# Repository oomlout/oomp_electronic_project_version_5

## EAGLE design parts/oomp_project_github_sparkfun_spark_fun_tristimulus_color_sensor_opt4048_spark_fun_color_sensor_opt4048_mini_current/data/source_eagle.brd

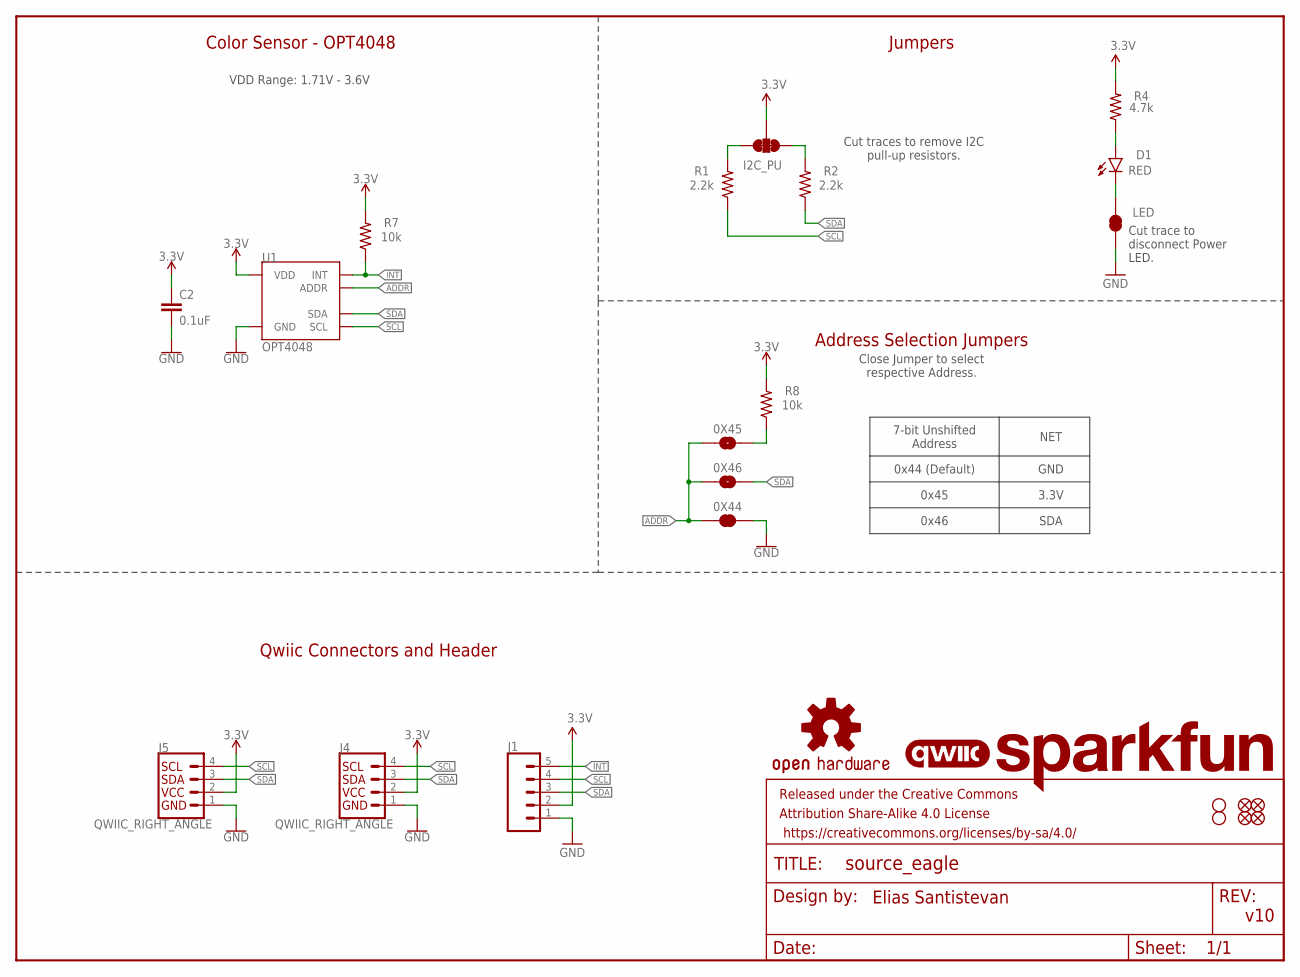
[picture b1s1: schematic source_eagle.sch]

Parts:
0X44: JUMPER-SMT_2_NC_TRACE_SILK; SMT-JUMPER_2_NC_TRACE_SILK
0X45, 0X46: JUMPER-SMT_2_NO_SILK; SMT-JUMPER_2_NO_SILK
C2: 0.1uF; 0402-TIGHT
D1: RED; LED-0603
FD5, FD6, FD7, FD8: FIDUCIALUFIDUCIAL; FIDUCIAL-MICRO
FRAME2: FRAME-LETTER; CREATIVE_COMMONS
H7, H8: STAND-OFFTIGHT; STAND-OFF-TIGHT
I2C_PU: S_MODE; SMT-JUMPER_3_2-NC_TRACE_SILK
J1: CONN_05NO_SILK; 1X05_NO_SILK
J4, J5: QWIIC_RIGHT_ANGLE; JST04_1MM_RA
LED: JUMPER-SMT_2_NC_TRACE_SILK; SMT-JUMPER_2_NC_TRACE_SILK
LOGO1: SFE_LOGO_NAMEBLANK; BLANK
LOGO2: QWIIC_LOGO_3MM; QWIIC_3MM
LOGO3: OSHW-LOGONO_SILK; DUMMY
R1, R2: 2.2k; 0603
R4: 4.7k; 0603
R7, R8: 10k; 0603
U1: OPT4048; FCSOT

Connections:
3.3V: C2.1, I2C_PU.2, J1.2, J4.2, J5.2, R4.2, R7.2, R8.2, U1.P1 (VDD)
ADDR: 0X44.1, 0X45.1, 0X46.1, U1.P2 (ADDR)
GND: 0X44.2, C2.2, J1.1, J4.1, J5.1, LED.1, U1.P4 (GND)
INT: J1.5, R7.1, U1.P7 (INT)
unnamed: I2C_PU.1, R1.2
unnamed: I2C_PU.3, R2.2
unnamed: D1.A, R4.1
unnamed: D1.C, LED.2
unnamed: 0X45.2, R8.1
SCL: J1.4, J4.4, J5.4, R1.1, U1.P5 (SCL)
SDA: 0X46.2, J1.3, J4.3, J5.3, R2.1, U1.P8 (SDA)

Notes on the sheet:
v10
Qwiic Connectors and Header
Elias Santistevan
Color Sensor - OPT4048
Cut traces to remove I2C pull-up resistors.
VDD Range: 1.71V - 3.6V
Jumpers
Cut trace to disconnect Power LED.
7-bit Unshifted Address
0x44 (Default)
0x45
0x46
GND
3.3V
SDA
NET
Address Selection Jumpers
Close Jumper to select respective Address.

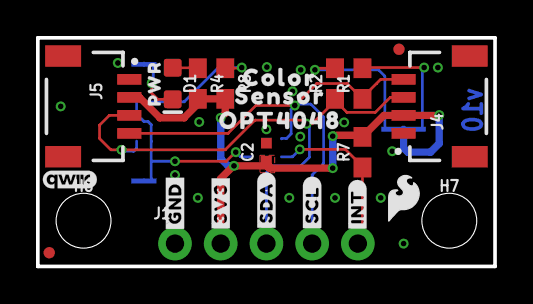
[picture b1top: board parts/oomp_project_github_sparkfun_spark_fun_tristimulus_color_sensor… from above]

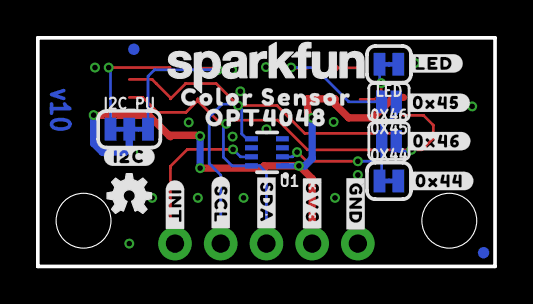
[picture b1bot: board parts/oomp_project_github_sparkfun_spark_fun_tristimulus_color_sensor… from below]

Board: 2 copper layers, 25.4 x 12.7 mm, 51 parts (22 on the bottom side), 11 nets.

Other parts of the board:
LOGO4: SPECIAL_INSTRUCTIONS-ORDERING; ORDERING_INSTRUCTIONS
U$1: #INT#9
U$2: COLOR_SENSOR227
U$3, U$12: OPT4048229
U$4: #0X44#11
U$5: #0X46#11
U$6: #0X45#11
U$7: #INT#3
U$8: SFE_LOGO_NAME_.1
U$9: COLOR14
U$10, U$37: #3V3#0
U$11: SENSOR15
U$13: #SDA#1
U$14: #LED#11
U$15: OSHW-LOGO-MINI
U$16, U$38: #GND#4
U$19, U$39: #SCL#5
U$20: #I2C#11
U$35: SFE_LOGO_FLAME_.1
U$40: #SDA#6
U$43: PWR8821882023

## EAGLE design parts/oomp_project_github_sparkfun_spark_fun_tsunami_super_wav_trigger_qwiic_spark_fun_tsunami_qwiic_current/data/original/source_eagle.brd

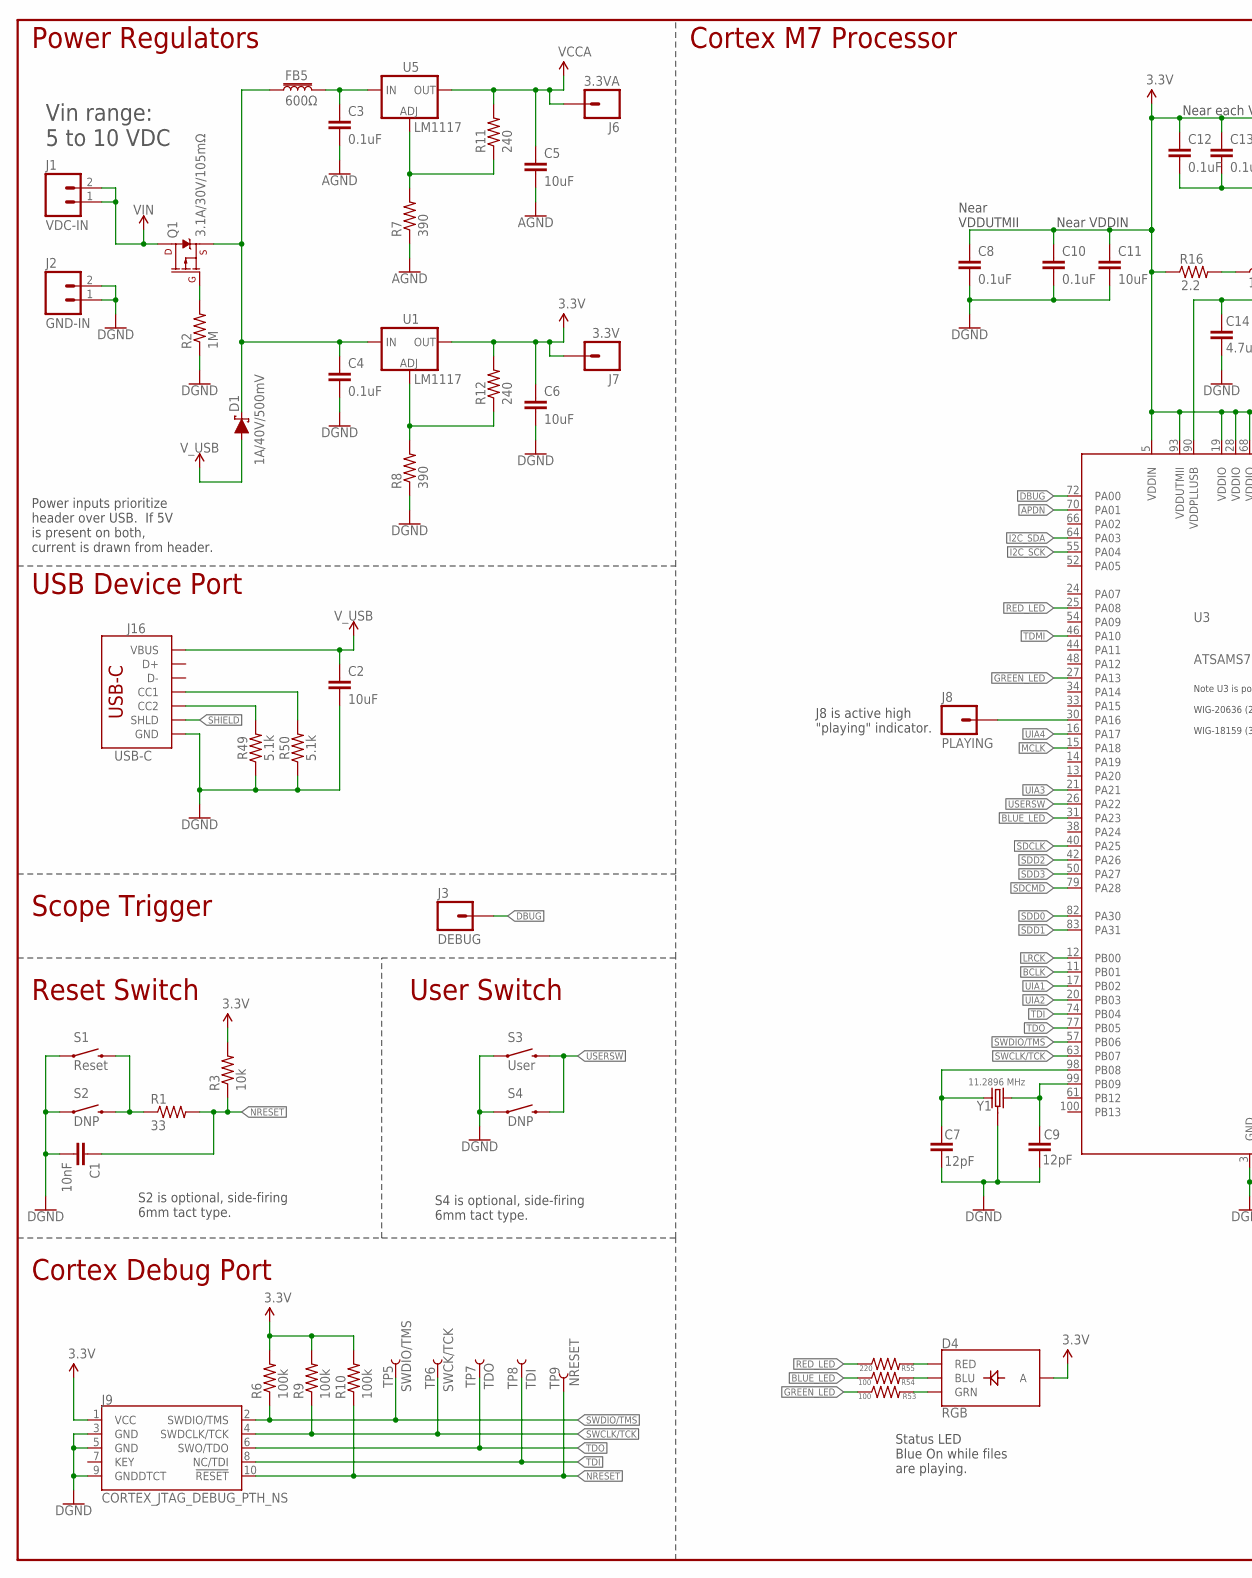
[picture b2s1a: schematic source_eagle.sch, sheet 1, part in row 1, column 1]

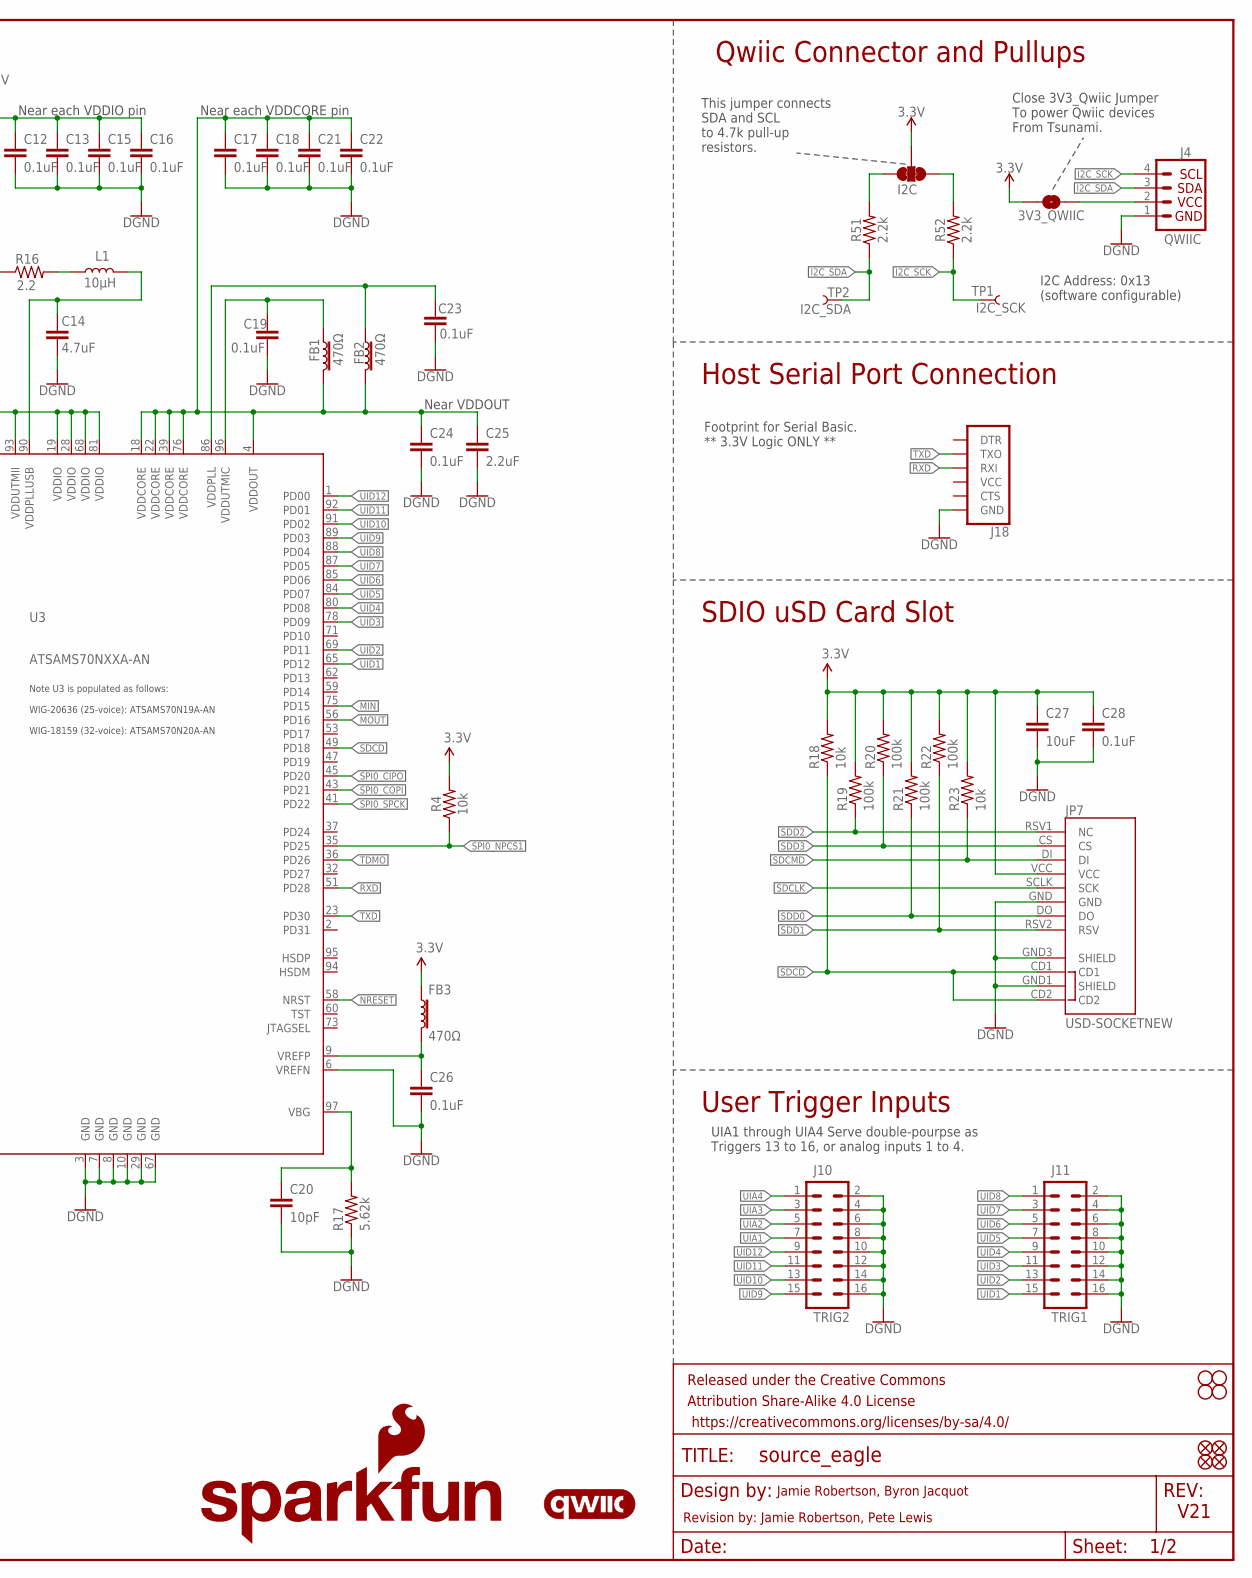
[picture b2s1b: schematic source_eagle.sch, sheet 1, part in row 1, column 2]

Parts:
3V3_QWIIC: JUMPER-SMT_2_NO_SILK; SMT-JUMPER_2_NO_SILK
C1: 10nF; 0402-TIGHT
C2, C5, C6, C11, C27: 10uF; 0402-TIGHT
C3, C4, C8, C10, C12, C13, C15, C16, C17, C18, C19, C21, C22, C23, C24, C26, C28: 0.1uF; 0402-TIGHT
C7, C9: 12pF; 0402-TIGHT
C14: 4.7uF; 0402-TIGHT
C20: 10pF; 0603
C25: 2.2uF; 0603
D1: 1A/40V/500mV; SMA-DIODE
D4: RGB; P-LCC-4-3
FB1, FB2, FB3: 470Ω; 0603
FB5: 600Ω; 0805
FD1, FD2, FD3, FD4: FIDUCIALUFIDUCIAL; FIDUCIAL-MICRO
FRAME1: FRAME-LEDGER; CREATIVE_COMMONS
H1, H2, H3, H4: STAND-OFF
I2C: JUMPER-SMT_3_2-NC_TRACE_SILK; SMT-JUMPER_3_2-NC_TRACE_SILK
J1: VDC-IN; 1X02_NO_SILK
J2: GND-IN; 1X02_NO_SILK
J3: DEBUG; 1X01_NO_SILK
J4: QWIIC; JST04_1MM_RA
J6: 3.3VA; 1X01_NO_SILK
J7: 3.3V; 1X01_NO_SILK
J8: PLAYING; 1X01_NO_SILK
J9: CORTEX_JTAG_DEBUG_PTH_NS; 2X5-PTH-1.27MM-NO_SILK
J10: TRIG2; 2X8_NOSILK
J11: TRIG1; 2X8_NOSILK
J16: USB-C; USB-C-16P-4LAYER-ISOLATED
J18: 6_PIN_SERIAL_TARGETSILK; 6_PIN_SERIAL_TARGET_SIDE_W_SILK
JP7: USD-SOCKETNEW; MICRO-SD-SOCKET-PP
L1: 10μH; 0805
LOGO2: SFE_LOGO_NAME_FLAME.2_INCH; SFE_LOGO_NAME_FLAME_.2
LOGO3: QWIIC_LOGO_4MM; QWIIC_4MM
Q1: 3.1A/30V/105mΩ; SOT23-3
R1: 33; 0603
R2: 1M; 0603
R3, R4, R18, R23: 10k; 0402-TIGHT
R6, R9, R10, R19, R20, R21, R22: 100k; 0402-TIGHT
R7, R8: 390; 0603
R11, R12: 240; 0603
R16: 2.2; 0603
R17: 5.62k; 0603
R49, R50: 5.1k; 0402-TIGHT
R51, R52: 2.2k; 0402-TIGHT
R53, R54: 100; 0603
R55: 220; 0603
S1: Reset; TACTILE_SWITCH_SMD_5.2MM
S2, S4: DNP; TACTILE_SWITCH_PTH_RIGHT_ANGLE
S3: User; TACTILE_SWITCH_SMD_5.2MM
TP1: I2C_SCK; TP_15TH
TP2: I2C_SDA; TP_15TH
TP5: SWDIO/TMS; TP_15TH
TP6: SWCK/TCK; TP_15TH
TP7: TDO; TP_15TH
TP8: TDI; TP_15TH
TP9: NRESET; TP_15TH
U1, U5: LM1117; SOT223
U3: ATSAMS70NXXA-AN; LQFP100
Y1: 11.2896 MHz; CRYSTAL-OSC-SMD-5X3

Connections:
3.3V: 3V3_QWIIC.1, C6.1, C8.1, C10.1, C11.1, C12.1, C13.1, C15.1, C16.1, C27.1, C28.1, D4.4 (A), FB3.1, I2C.2, J7.1, J9.1 (VCC), JP7.VCC, R3.2, R4.2, R6.2, R9.2, R10.2, R12.2, R16.1, R18.2, R19.2, R20.2, R21.2, R22.2, R23.2, U1.2 (OUT), U1.4 (OUT), U3.5 (VDDIN), U3.19 (VDDIO), U3.28 (VDDIO), U3.68 (VDDIO), U3.81 (VDDIO), U3.93 (VDDUTMII); also elsewhere on the board
AGND: C3.2, C5.2, R7.1; also elsewhere on the board
APDN: U3.70 (PA01); also elsewhere on the board
BCLK: U3.11 (PB01); also elsewhere on the board
BLUE_LED: R54.1, U3.31 (PA23)
CC1: J16.A5 (CC1), R50.2
CC2: J16.B5 (CC2), R49.2
DBUG: J3.1, U3.72 (PA00)
DGND: C1.2, C2.2, C4.2, C6.2, C7.2, C8.2, C9.2, C10.2, C11.2, C12.2, C13.2, C14.2, C15.2, C16.2, C17.2, C18.2, C19.2, C20.2, C21.2, C22.2, C23.2, C24.2, C25.2, C26.2, C27.2, C28.2, J2.1, J2.2, J4.1, J9.3 (GND), J9.5 (GND), J9.9 (GNDDTCT), J10.2, J10.4, J10.6, J10.8, J10.10, J10.12, J10.14, J10.16, J11.2, J11.4, J11.6, J11.8, J11.10, J11.12, J11.14, J11.16, J16.GND, J16.GND2 (GND), J18.6 (GND), JP7.GND, JP7.GND1 (SHIELD), JP7.GND3 (SHIELD), R2.1, R8.1, R17.1, R49.1, R50.1, S1.1, S2.1, S3.1, S4.1, U3.3 (GND), U3.6 (VREFN), U3.7 (GND), U3.8 (GND), U3.10 (GND), U3.29 (GND), U3.67 (GND), Y1.2 (3), Y1.4 (3); also elsewhere on the board
GREEN_LED: R53.1, U3.27 (PA13)
I2C_SCK: J4.4, R52.1, TP1.1, U3.55 (PA04)
I2C_SDA: J4.3, R51.1, TP2.1, U3.64 (PA03)
LRCK: U3.12 (PB00); also elsewhere on the board
MCLK: U3.15 (PA18); also elsewhere on the board
MIN: U3.75 (PD15); also elsewhere on the board
MOUT: U3.56 (PD16); also elsewhere on the board
unnamed: C7.1, U3.98 (PB08), Y1.1
unnamed: C9.1, U3.99 (PB09), Y1.3 (2)
unnamed: C19.1, FB1.1, U3.96 (VDDUTMIC)
unnamed: C14.1, L1.2, U3.90 (VDDPLLUSB)
unnamed: C23.1, FB2.1, U3.86 (VDDPLL)
unnamed: I2C.3, R51.2
unnamed: J8.1, U3.30 (PA16)
unnamed: I2C.1, R52.2
unnamed: C20.1, R17.2, U3.97 (VBG)
unnamed: C26.1, FB3.2, U3.9 (VREFP)
unnamed: L1.1, R16.2
unnamed: R7.2, R11.1, U5.1 (ADJ)
unnamed: R1.1, S1.3 (2), S2.2
unnamed: R8.2, R12.1, U1.1 (ADJ)
unnamed: 3V3_QWIIC.2, J4.2
unnamed: D4.2 (GRN), R53.2
unnamed: D4.3 (BLU), R54.2
unnamed: D4.1 (RED), R55.2
unnamed: C3.1, FB5.2, U5.3 (IN)
unnamed: Q1.1 (G), R2.2
NRESET: C1.1, J9.10 (!RESET), R1.2, R3.1, R10.1, TP9.1, U3.58 (NRST)
RED_LED: R55.1, U3.25 (PA08)
REGINPUTS: C4.1, D1.C, FB5.1, Q1.2 (S), U1.3 (IN)
RXD: J18.3 (RXI), U3.51 (PD28)
SDCD: JP7.CD1, JP7.CD2, R18.1, U3.49 (PD18)
SDCLK: JP7.SCLK (SCK), U3.40 (PA25)
SDCMD: JP7.DI, R23.1, U3.79 (PA28)
SDD0: JP7.DO, R21.1, U3.82 (PA30)
SDD1: JP7.RSV2 (RSV), R22.1, U3.83 (PA31)
SDD2: JP7.RSV1 (NC), R19.1, U3.42 (PA26)
SDD3: JP7.CS, R20.1, U3.50 (PA27)
SHIELD: J16.SHLD1 (SHLD), J16.SHLD2 (SHLD), J16.SHLD3 (SHLD), J16.SHLD4 (SHLD), J16.SHLD5 (SHLD), J16.SHLD6 (SHLD), J16.SHLD7 (SHLD), J16.SHLD8 (SHLD)
SPI0_CIPO: U3.45 (PD20); also elsewhere on the board
SPI0_COPI: U3.43 (PD21); also elsewhere on the board
SPI0_NPCS1: R4.1, U3.35 (PD25); also elsewhere on the board
SPI0_SPCK: U3.41 (PD22); also elsewhere on the board
SWCLK/TCK: J9.4 (SWDCLK/TCK), R9.1, TP6.1, U3.63 (PB07)
SWDIO/TMS: J9.2 (SWDIO/TMS), R6.1, TP5.1, U3.57 (PB06)
TDI: J9.8 (NC/TDI), TP8.1, U3.74 (PB04)
TDMI: U3.46 (PA10); also elsewhere on the board
TDMO: U3.36 (PD26); also elsewhere on the board
TDO: J9.6 (SWO/TDO), TP7.1, U3.77 (PB05)
TXD: J18.2 (TXO), U3.23 (PD30)
UIA1: J10.7, U3.17 (PB02)
UIA2: J10.5, U3.20 (PB03)
UIA3: J10.3, U3.21 (PA21)
UIA4: J10.1, U3.16 (PA17)
UID1: J11.15, U3.65 (PD12)
UID2: J11.13, U3.69 (PD11)
UID3: J11.11, U3.78 (PD09)
UID4: J11.9, U3.80 (PD08)
UID5: J11.7, U3.84 (PD07)
UID6: J11.5, U3.85 (PD06)
UID7: J11.3, U3.87 (PD05)
UID8: J11.1, U3.88 (PD04)
UID9: J10.15, U3.89 (PD03)
UID10: J10.13, U3.91 (PD02)
UID11: J10.11, U3.92 (PD01)
UID12: J10.9, U3.1 (PD00)
USERSW: S3.3 (2), S4.2, U3.26 (PA22)
VCCA: C5.1, J6.1, R11.2, U5.2 (OUT), U5.4 (OUT); also elsewhere on the board
VDDOUT: C17.1, C18.1, C21.1, C22.1, C24.1, C25.1, FB1.2, FB2.2, U3.4 (VDDOUT), U3.18 (VDDCORE), U3.22 (VDDCORE), U3.39 (VDDCORE), U3.76 (VDDCORE)
VIN: J1.1, J1.2, Q1.3 (D)
V_USB: C2.1, D1.A, J16.VBUS1 (VBUS), J16.VBUS2 (VBUS)

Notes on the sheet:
Jamie Robertson, Byron Jacquot
V21
Near each VDDCORE pin
Near each VDDIO pin
Near VDDUTMII
Near VDDIN
Near VDDOUT
Power Regulators
USB Device Port
Scope Trigger
Cortex Debug Port
Cortex M7 Processor
SDIO uSD Card Slot
User Trigger Inputs
Reset Switch
S2 is optional, side-firing 6mm tact type.
Vin range: 5 to 10 VDC
Status LED Blue On while files are playing.
Power inputs prioritize header over USB. If 5V is present on both, current is drawn from header.
UIA1 through UIA4 Serve double-pourpse as Triggers 13 to 16, or analog inputs 1 to 4.
Host Serial Port Connection
Footprint for Serial Basic. ** 3.3V Logic ONLY **
User Switch
J8 is active high "playing" indicator.
S4 is optional, side-firing 6mm tact type.
This jumper connects SDA and SCL to 4.7k pull-up resistors.
Revision by: Jamie Robertson, Pete Lewis
Qwiic Connector and Pullups
Close 3V3_Qwiic Jumper To power Qwiic devices From Tsunami.
I2C Address: 0x13 (software configurable)
Note U3 is populated as follows: WIG-20636 (25-voice): ATSAMS70N19A-AN WIG-18159 (32-voice): ATSAMS70N20A-AN

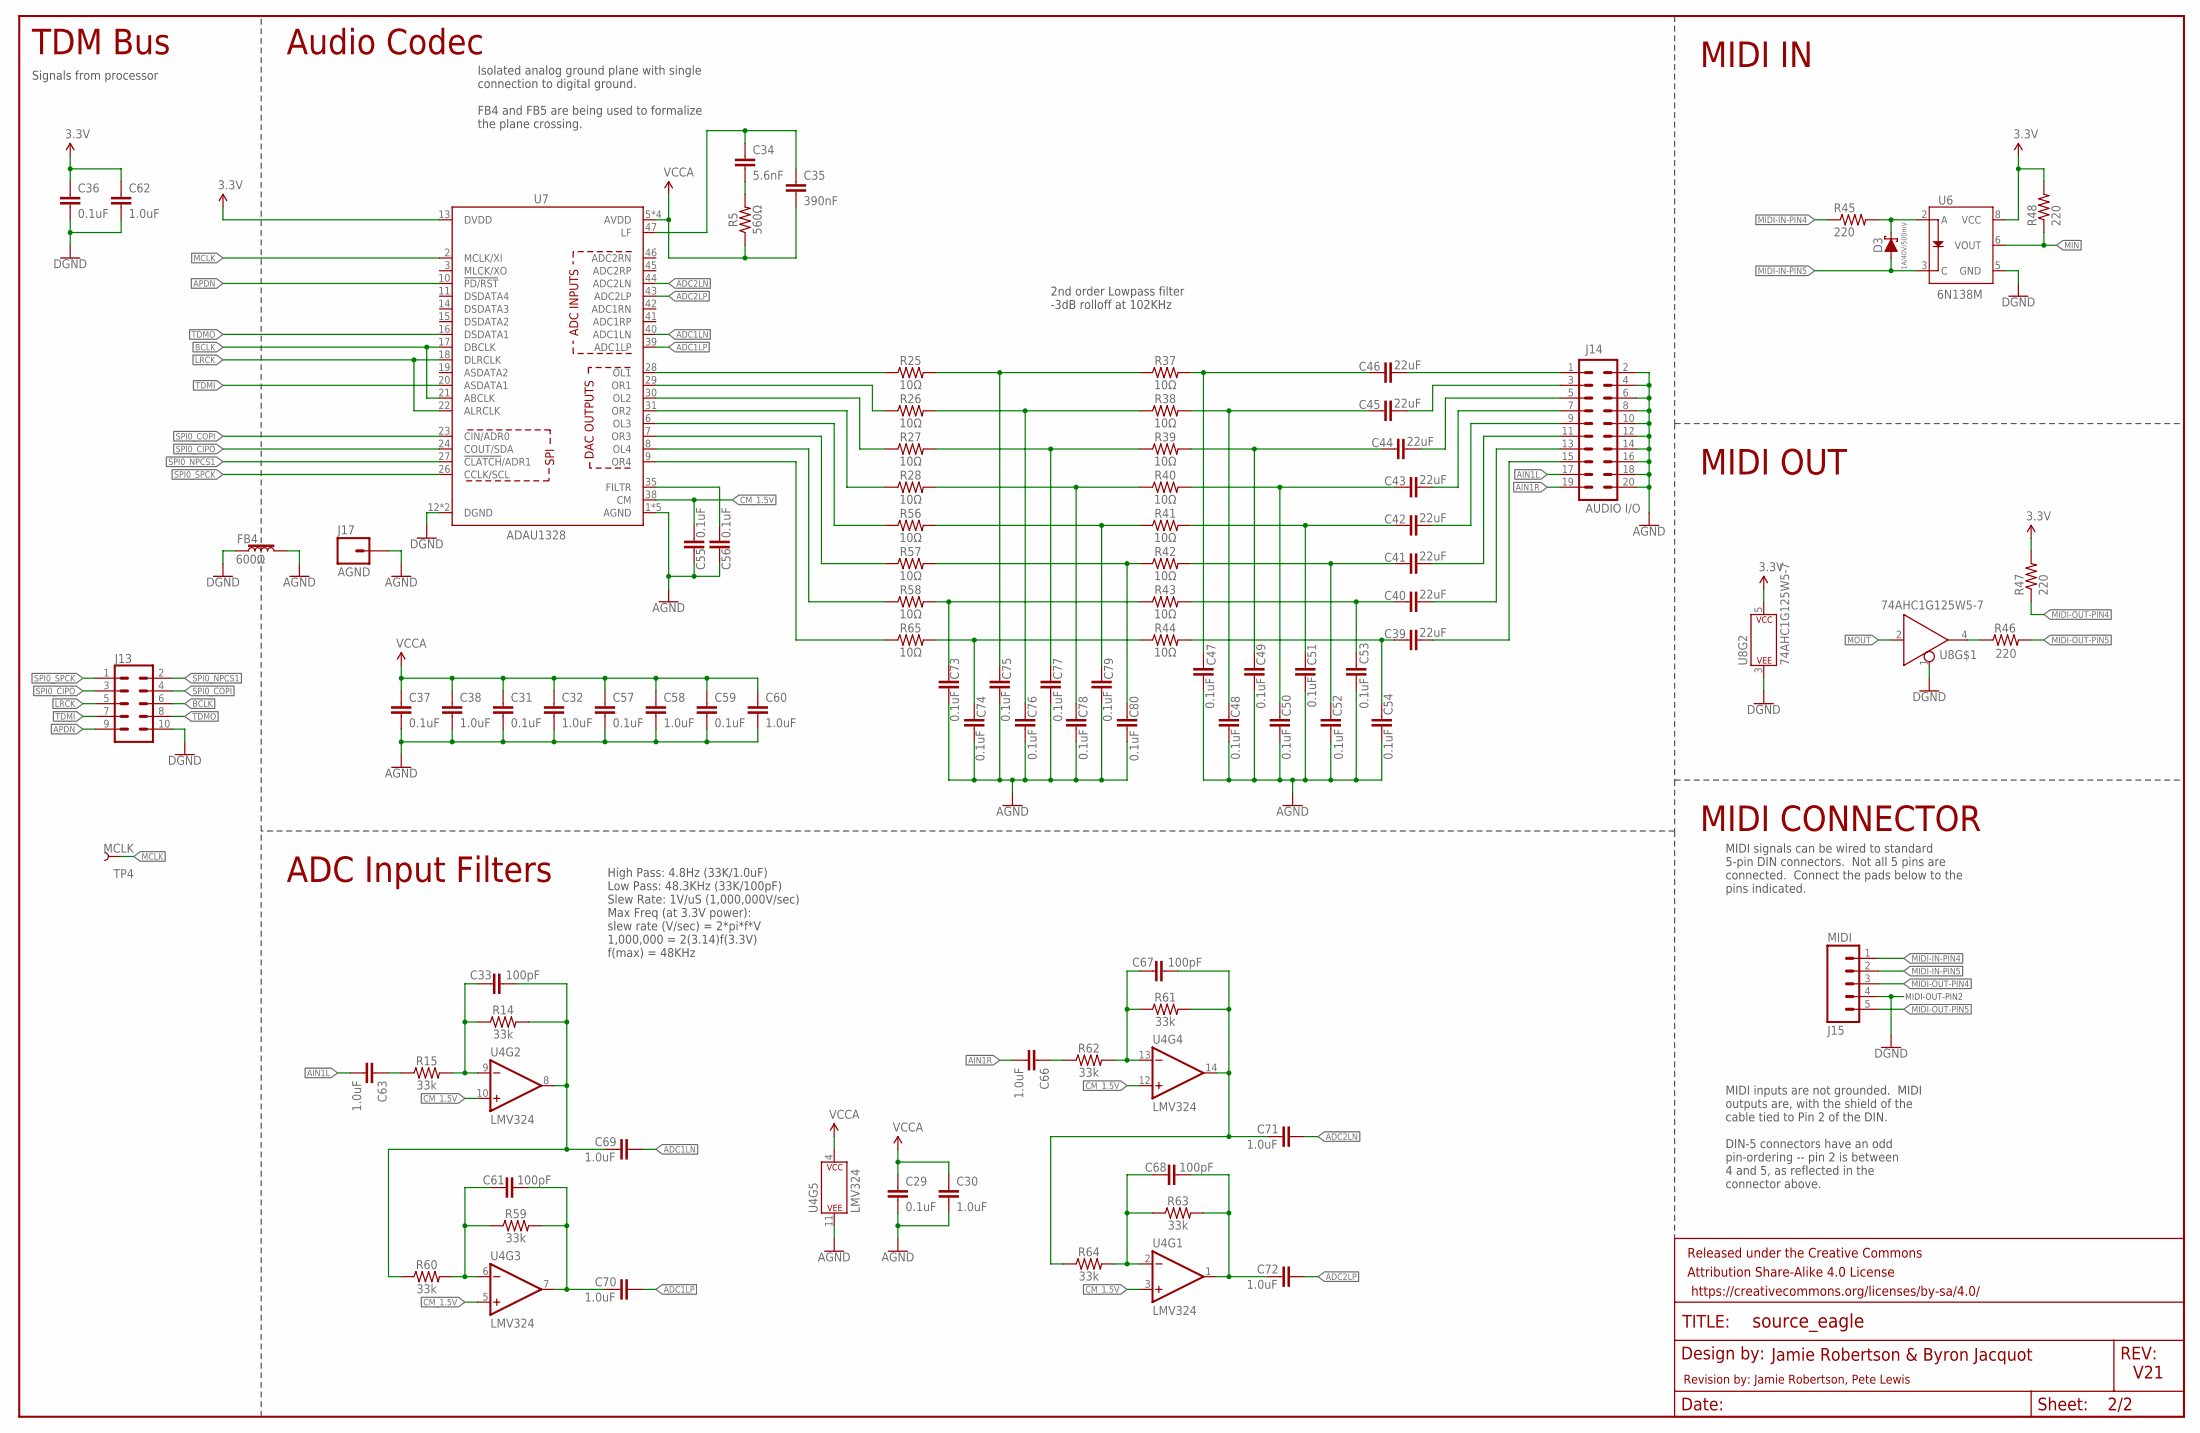
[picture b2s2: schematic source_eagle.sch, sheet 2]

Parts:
C29, C31, C36, C37, C47, C48, C49, C50, C51, C52, C53, C54, C55, C56, C57, C59, C73, C74, C75, C76, C77, C78, C79, C80: 0.1uF; 0402-TIGHT
C30, C32, C38, C58, C60, C62, C63, C66, C69, C70, C71, C72: 1.0uF; 0402-TIGHT
C33, C61, C67, C68: 100pF; 0402-TIGHT
C34: 5.6nF; 0603
C35: 390nF; 0603
C39, C40, C41, C42, C43, C44, C45, C46: 22uF; 0805
D3: 1A/40V/500mV; SMA-DIODE
FB4: 600Ω; 0805
FRAME2: FRAME-LEDGER; CREATIVE_COMMONS
J13: CONN_05X2NO_SILK; 2X5_NOSILK
J14: AUDIO I/O; 2X10_NOSILK
J15: MIDI; 1X05_NO_SILK
J17: AGND; 1X01_NO_SILK
R5: 560Ω; 0402-TIGHT
R14, R15, R59, R60, R61, R62, R63, R64: 33k; 0402-TIGHT
R25, R26, R27, R28, R37, R38, R39, R40, R41, R42, R43, R44, R56, R57, R58, R65: 10Ω; 0402-TIGHT
R45, R46, R47, R48: 220; 0603
TP4: MCLK; TP_15TH
U4: LMV324; SO14
U6: 6N138M; 8-SMD
U7: ADAU1328; LQFP-48
U8: 74AHC1G125W5-7; SOT23-5

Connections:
3.3V: C36.1, C62.1, R47.2, R48.2, U6.8 (VCC), U7.13 (DVDD), U8.5 (P$V+); also elsewhere on the board
56: D3.C, R45.2, U6.2 (A)
ADC1LN: C69.1, U7.40 (ADC1LN)
ADC1LP: C70.1, U7.39 (ADC1LP)
ADC2LN: C71.1, U7.44 (ADC2LN)
ADC2LP: C72.1, U7.43 (ADC2LP)
AGND: C29.2, C30.2, C31.2, C32.2, C37.2, C38.2, C47.2, C48.2, C49.2, C50.2, C51.2, C52.2, C53.2, C54.2, C55.2, C56.2, C57.2, C58.2, C59.2, C60.2, C73.1, C74.1, C75.1, C76.1, C77.1, C78.1, C79.1, C80.1, FB4.2, J14.2, J14.4, J14.6, J14.8, J14.10, J14.12, J14.14, J14.16, J14.18, J14.20, J17.1, U4.11 (P$V-), U7.1 (AGND), U7.4 (AGND), U7.32 (AGND), U7.34 (AGND), U7.36 (AGND); also elsewhere on the board
AIN1L: C63.2, J14.17
AIN1R: C66.2, J14.19
AOUT1L: C46.1, C47.1, R37.2
AOUT1R: C45.1, C48.1, R38.2
AOUT2L: C44.2, J14.5
AOUT2R: C43.1, C50.1, R40.2
AOUT3L: C42.2, J14.9
AOUT3R: C41.1, C52.1, R42.2
AOUT4L: C40.1, C53.1, R43.2
AOUT4R: C39.1, C54.1, R44.2
APDN: J13.9, U7.10 (!PD/RST!); also elsewhere on the board
BCLK: J13.6, U7.17 (DBCLK), U7.21 (ABCLK); also elsewhere on the board
CM_1.5V: C55.1, U4.3 (+IN), U4.5 (+IN), U4.10 (+IN), U4.12 (+IN), U7.38 (CM)
DGND: C36.2, C62.2, FB4.1, J13.10, J15.4, U6.5 (GND), U7.12 (DGND), U7.25 (DGND), U8.1 (!EN), U8.3 (P$V-); also elsewhere on the board
LF: C34.1, C35.1, U7.47 (LF)
LRCK: J13.5, U7.18 (DLRCLK), U7.22 (ALRCLK); also elsewhere on the board
MCLK: TP4.1, U7.2 (MCLK/XI); also elsewhere on the board
MIDI-IN-PIN4: J15.1, R45.1
MIDI-IN-PIN5: D3.A, J15.2, U6.3 (C)
MIDI-OUT-PIN4: J15.3, R47.1
MIDI-OUT-PIN5: J15.5, R46.2
MIN: R48.1, U6.6 (VOUT); also elsewhere on the board
MOUT: U8.2 (A); also elsewhere on the board
unnamed: C33.2, C69.2, R14.2, R60.1, U4.8 (OUT)
unnamed: C34.2, R5.2
unnamed: C63.1, R15.1
unnamed: C61.2, C70.2, R59.2, U4.7 (OUT)
unnamed: C68.2, C72.2, R63.2, U4.1 (OUT)
unnamed: C39.2, J14.15
unnamed: C40.2, J14.13
unnamed: C41.2, J14.11
unnamed: C42.1, C51.1, R41.2
unnamed: C43.2, J14.7
unnamed: C75.2, R25.2, R37.1
unnamed: C74.2, R44.1, R65.2
unnamed: C73.2, R43.1, R58.2
unnamed: C80.2, R42.1, R57.2
unnamed: C44.1, C49.1, R39.2
unnamed: C46.2, J14.1
unnamed: C45.2, J14.3
unnamed: R46.1, U8.4 (Y)
unnamed: C56.1, U7.35 (FILTR)
unnamed: C61.1, R59.1, R60.2, U4.6 (-IN)
unnamed: C33.1, R14.1, R15.2, U4.9 (-IN)
unnamed: C79.2, R41.1, R56.2
unnamed: C78.2, R28.2, R40.1
unnamed: C76.2, R26.2, R38.1
unnamed: C77.2, R27.2, R39.1
unnamed: C67.2, C71.2, R61.2, R64.1, U4.14 (OUT)
unnamed: C66.1, R62.1
unnamed: C68.1, R63.1, R64.2, U4.2 (-IN)
unnamed: C67.1, R61.1, R62.2, U4.13 (-IN)
OL1: R25.1, U7.28 (OL1)
OL2: R27.1, U7.30 (OL2)
OL3: R56.1, U7.6 (OL3)
OL4: R58.1, U7.8 (OL4)
OR1: R26.1, U7.29 (OR1)
OR2: R28.1, U7.31 (OR2)
OR3: R57.1, U7.7 (OR3)
OR4: R65.1, U7.9 (OR4)
SPI0_CIPO: J13.3, U7.24 (COUT/SDA); also elsewhere on the board
SPI0_COPI: J13.4, U7.23 (CIN/ADR0); also elsewhere on the board
SPI0_NPCS1: J13.2, U7.27 (!CLATCH!/ADR1); also elsewhere on the board
SPI0_SPCK: J13.1, U7.26 (CCLK/SCL); also elsewhere on the board
TDMI: J13.7, U7.20 (ASDATA1); also elsewhere on the board
TDMO: J13.8, U7.16 (DSDATA1); also elsewhere on the board
VCCA: C29.1, C30.1, C31.1, C32.1, C35.2, C37.1, C38.1, C57.1, C58.1, C59.1, C60.1, R5.1, U4.4 (P$V+), U7.5 (AVDD), U7.33 (AVDD), U7.37 (AVDD), U7.48 (AVDD); also elsewhere on the board

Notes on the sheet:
Isolated analog ground plane with single connection to digital ground. FB4 and FB5 are being used to formalize the plane crossing.
Audio Codec
MIDI IN
MIDI OUT
Jamie Robertson & Byron Jacquot
V21
TDM Bus
Signals from processor
MIDI CONNECTOR
MIDI signals can be wired to standard 5-pin DIN connectors. Not all 5 pins are connected. Connect the pads below to the pins indicated.
MIDI-OUT-PIN2
MIDI inputs are not grounded. MIDI outputs are, with the shield of the cable tied to Pin 2 of the DIN. DIN-5 connectors have an odd pin-ordering -- pin 2 is between 4 and 5, as reflected in the connector above.
2nd order Lowpass filter -3dB rolloff at 102KHz
ADC Input Filters
High Pass: 4.8Hz (33K/1.0uF) Low Pass: 48.3KHz (33K/100pF) Slew Rate: 1V/uS (1,000,000V/sec) Max Freq (at 3.3V power): slew rate (V/sec) = 2*pi*f*V 1,000,000 = 2(3.14)f(3.3V) f(max) = 48KHz
Revision by: Jamie Robertson, Pete Lewis

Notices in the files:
parts and their libraries:
SparkFun-Aesthetics: Licensing: Creative Commons ShareAlike 4.0 International - https://creativecommons.org/licenses/by-sa/4.0
SparkFun-Aesthetics: Released under the Creative Commons Attribution Share-Alike 4.0 License
SparkFun-Aesthetics: https://creativecommons.org/licenses/by-sa/4.0
